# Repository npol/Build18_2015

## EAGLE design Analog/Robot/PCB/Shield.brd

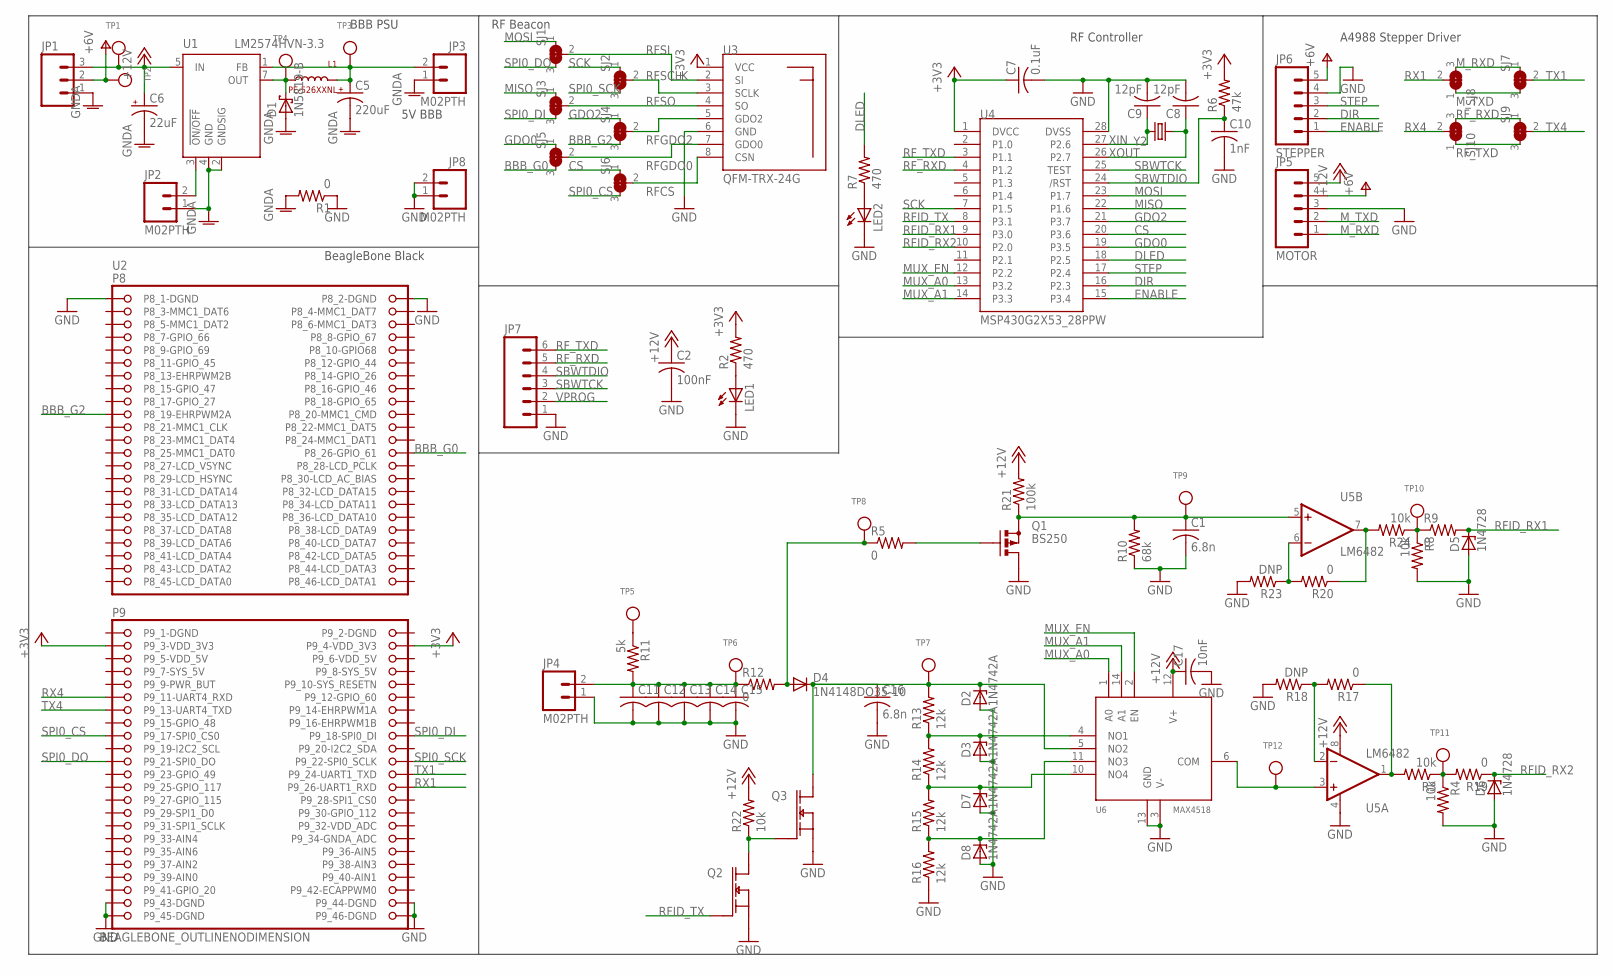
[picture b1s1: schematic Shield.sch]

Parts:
C1, C16: 6.8n; C0805
C2: 100nF; C0805
C5: 220uF; E3,5-8
C6: 22uF; E2,5-5
C7: 0.1uF; C0805
C8, C9: 12pF; C0805
C10: 1nF; C0805
C11, C12, C13, C14, C15: C-USC0805; C0805
C17: 10nF; C0805
D1: 1N5819-B; DO41-7.6
D2, D3, D7, D8: 1N4742A; DO41Z10
D4: 1N4148DO35-10; DO35-10
D5, D6: 1N4728; DO41Z10
JP1: M03PTH; 1X03
JP2, JP3, JP4, JP8: M02PTH; 1X02
JP5: MOTOR; 1X05
JP6: STEPPER; 1X05
JP7: M06SIP; 1X06
L1: PE-526XXNL; PE_VERTICAL
LED1, LED2: LEDCHIP-LED0805; CHIP-LED0805
Q1: BS250; SOT54E
Q2, Q3: 2N7002_SINGLESOT23/TO-236AB; TO-236AB
R1, R5, R9, R12, R17, R19, R20: 0; R0805
R2, R7: 470; R0805
R3, R4, R8, R22, R24: 10k; R0805
R6: 47k; R0805
R10: 68k; R0805
R11: 5k; R0805
R13, R14, R15, R16: 12k; R0805
R18, R23: DNP; R0805
R21: 100k; R0805
SJ1, SJ2, SJ3, SJ4, SJ5, SJ6, SJ7, SJ8, SJ9, SJ10: SOLDERJUMPER_2WAY0805; SOLDERJUMPER_2WAY_OPEN_0805
TP1, TP2, TP3, TP4, TP5, TP6, TP7, TP8, TP9, TP10, TP11, TP12: TESTPOINT0.1"; 1X01_ROUND
U1: LM2574HVN-3.3; DIL08
U2: BEAGLEBONE_OUTLINENODIMENSION; BEAGLEBONE_SHIELD_NODIMENSION
U3: QFM-TRX-24G; QFM-TRX1-24G
U4: MSP430G2X53_28PPW; PW(R-PDSO-G28)
U5: LM6482; SOIC8
U6: MAX4518; SO-14
Y2: CRYSTALHC49UV; HC49U-V

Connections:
+3V3: C7.1, R2.2, R6.2, U2.9.3 (P9_3-VDD_3V3), U2.9.4 (P9_4-VDD_3V3), U3.1 (VCC), U4.1 (DVCC)
+12V: C2.1, C6.+, C17.1, JP1.3, JP5.5, R21.2, R22.2, TP1.1, U1.5 (IN), U5.8 (V+), U6.12 (V+)
BBB_G0: SJ5.3, U2.8.26 (P8_26-GPIO_61)
BBB_G2: SJ4.3, U2.8.19 (P8_19-EHRPWM2A)
CS: SJ6.1, U4.20 (P3.6)
DIR: JP6.2, U4.16 (P2.3)
DLED: R7.2, U4.18 (P2.5)
ENABLE: JP6.1, U4.15 (P3.4)
GDO0: SJ5.1, U4.19 (P3.5)
GDO2: SJ4.1, U4.21 (P3.7)
GND: C1.2, C2.2, C7.2, C8.2, C9.2, C10.2, C11.2, C12.2, C13.2, C14.2, C15.2, C16.2, C17.2, D2.A, D3.A, D5.A, D6.A, D7.A, D8.A, JP4.1, JP5.3, JP6.4, JP7.1, JP8.1, JP8.2, LED1.C, LED2.C, Q1.D, Q2.2 (S), Q3.2 (S), R1.1, R4.2, R8.2, R10.1, R16.1, R18.2, R23.2, U2.8.1 (P8_1-DGND), U2.8.2 (P8_2-DGND), U2.9.43 (P9_43-DGND), U2.9.44 (P9_44-DGND), U2.9.45 (P9_45-DGND), U2.9.46 (P9_46-DGND), U3.6 (GND), U4.28 (DVSS), U5.4 (V-), U6.3 (V-), U6.13 (GND)
GNDA: C5.-, C6.-, D1.A, JP1.1, JP2.1, JP3.1, R1.2, U1.2 (GNDSIG), U1.4 (GND)
MISO: SJ3.1, U4.22 (P1.6)
MOSI: SJ1.1, U4.23 (P1.7)
MUX_A0: U4.13 (P3.2), U6.1 (A0)
MUX_A1: U4.14 (P3.3), U6.14 (A1)
MUX_EN: U4.12 (P2.2), U6.2 (EN)
M_RXD: JP5.1, SJ7.1, SJ8.3
M_TXD: JP5.2, SJ7.3, SJ8.1
unnamed: R11.1, TP5.1
unnamed: LED2.A, R7.1
unnamed: D1.C, L1.2, TP4.1, U1.7 (OUT)
unnamed: C5.+, JP3.2, L1.1, TP3.1, U1.1 (FB)
unnamed: JP2.2, U1.3 (!ON/OFF)
unnamed: TP12.1, U5.3 (+IN), U6.6 (COM)
unnamed: C11.1, C12.1, C13.1, C14.1, C15.1, JP4.2, R11.2, R12.1, TP6.1
unnamed: D4.A, R5.1, R12.2, TP8.1
unnamed: C16.1, D2.C, D4.C, Q3.3 (D), R13.2, TP7.1, U6.5 (NO2)
unnamed: R20.2, R23.1, U5.6 (-IN)
unnamed: R20.1, R24.2, U5.7 (OUT)
unnamed: R17.2, R18.1, U5.2 (-IN)
unnamed: R8.1, R9.1, R24.1, TP10.1
unnamed: R3.2, R17.1, U5.1 (OUT)
unnamed: R3.1, R4.1, R19.2, TP11.1
unnamed: D3.C, R13.1, R14.2, U6.4 (NO1)
unnamed: D7.C, R14.1, R15.2, U6.10 (NO4)
unnamed: D8.C, R15.1, R16.2, U6.11 (NO3)
unnamed: C1.1, Q1.S, R10.2, R21.1, TP9.1, U5.5 (+IN)
unnamed: Q2.3 (D), Q3.1 (G), R22.1
unnamed: Q1.G, R5.2
unnamed: LED1.A, R2.1
P9_1-DGND: U2.9.1 (P9_1-DGND)
P9_2-DGND: U2.9.2 (P9_2-DGND)
P9_5-VDD_5V: U2.9.5 (P9_5-VDD_5V)
P9_6-VDD_5V: U2.9.6 (P9_6-VDD_5V)
P9_7-SYS_5V: U2.9.7 (P9_7-SYS_5V)
P9_39-AIN0: U2.9.39 (P9_39-AIN0)
RFCS: SJ6.2, U3.8 (CSN)
RFGDO0: SJ5.2, U3.7 (GDO0)
RFGDO2: SJ4.2, U3.5 (GDO2)
RFID_RX1: D5.C, R9.2, U4.9 (P3.0)
RFID_RX2: D6.C, R19.1, U4.10 (P2.0)
RFID_TX: Q2.1 (G), U4.8 (P3.1)
RFSCLK: SJ2.2, U3.3 (SCLK)
RFSI: SJ1.2, U3.2 (SI)
RFSO: SJ3.2, U3.4 (SO)
RF_RXD: JP7.5, SJ9.1, SJ10.3, U4.4 (P1.2)
RF_TXD: JP7.6, SJ9.3, SJ10.1, U4.3 (P1.1)
RX1: SJ8.2, U2.9.26 (P9_26-UART1_RXD)
RX4: SJ10.2, U2.9.11 (P9_11-UART4_RXD)
SBWTCK: JP7.3, U4.25 (TEST)
SBWTDIO: C10.1, JP7.4, R6.1, U4.24 (/RST)
SCK: SJ2.1, U4.7 (P1.5)
SPI0_CS: SJ6.3, U2.9.17 (P9_17-SPI0_CS0)
SPI0_DI: SJ3.3, U2.9.18 (P9_18-SPI0_DI)
SPI0_DO: SJ1.3, U2.9.21 (P9_21-SPI0_DO)
SPI0_SCK: SJ2.3, U2.9.22 (P9_22-SPI0_SCLK)
STEP: JP6.3, U4.17 (P2.4)
TX1: SJ7.2, U2.9.24 (P9_24-UART1_TXD)
TX4: SJ9.2, U2.9.13 (P9_13-UART4_TXD)
V+: JP1.2, JP5.4, JP6.5, TP2.1
VPROG: JP7.2
XIN: C9.1, U4.27 (P2.6), Y2.2
XOUT: C8.1, U4.26 (P2.7), Y2.1

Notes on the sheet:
RF Controller
5V BBB
RF Beacon
A4988 Stepper Driver
BBB PSU
BeagleBone Black

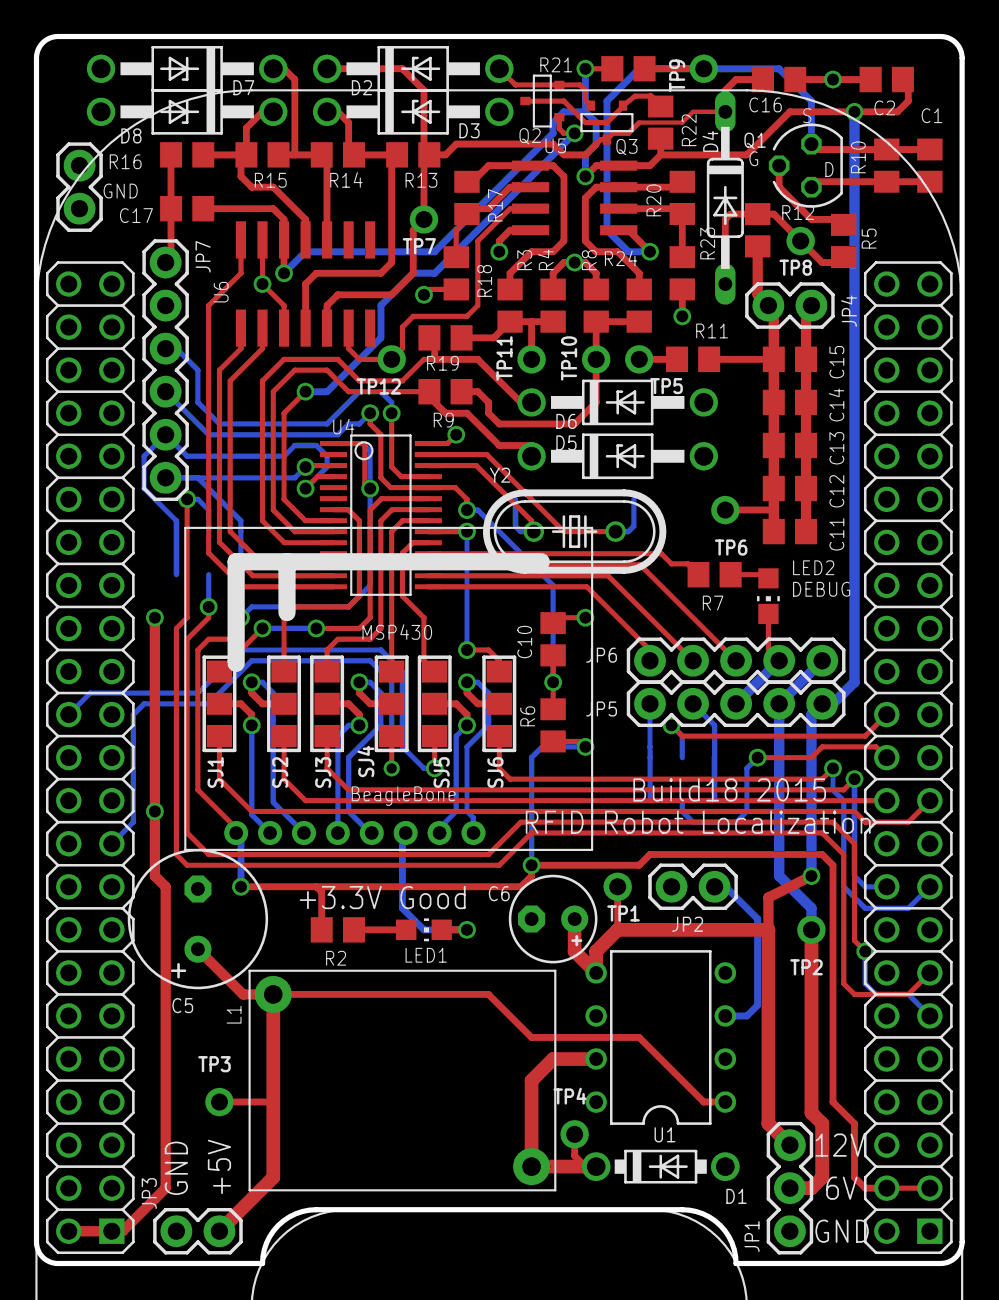
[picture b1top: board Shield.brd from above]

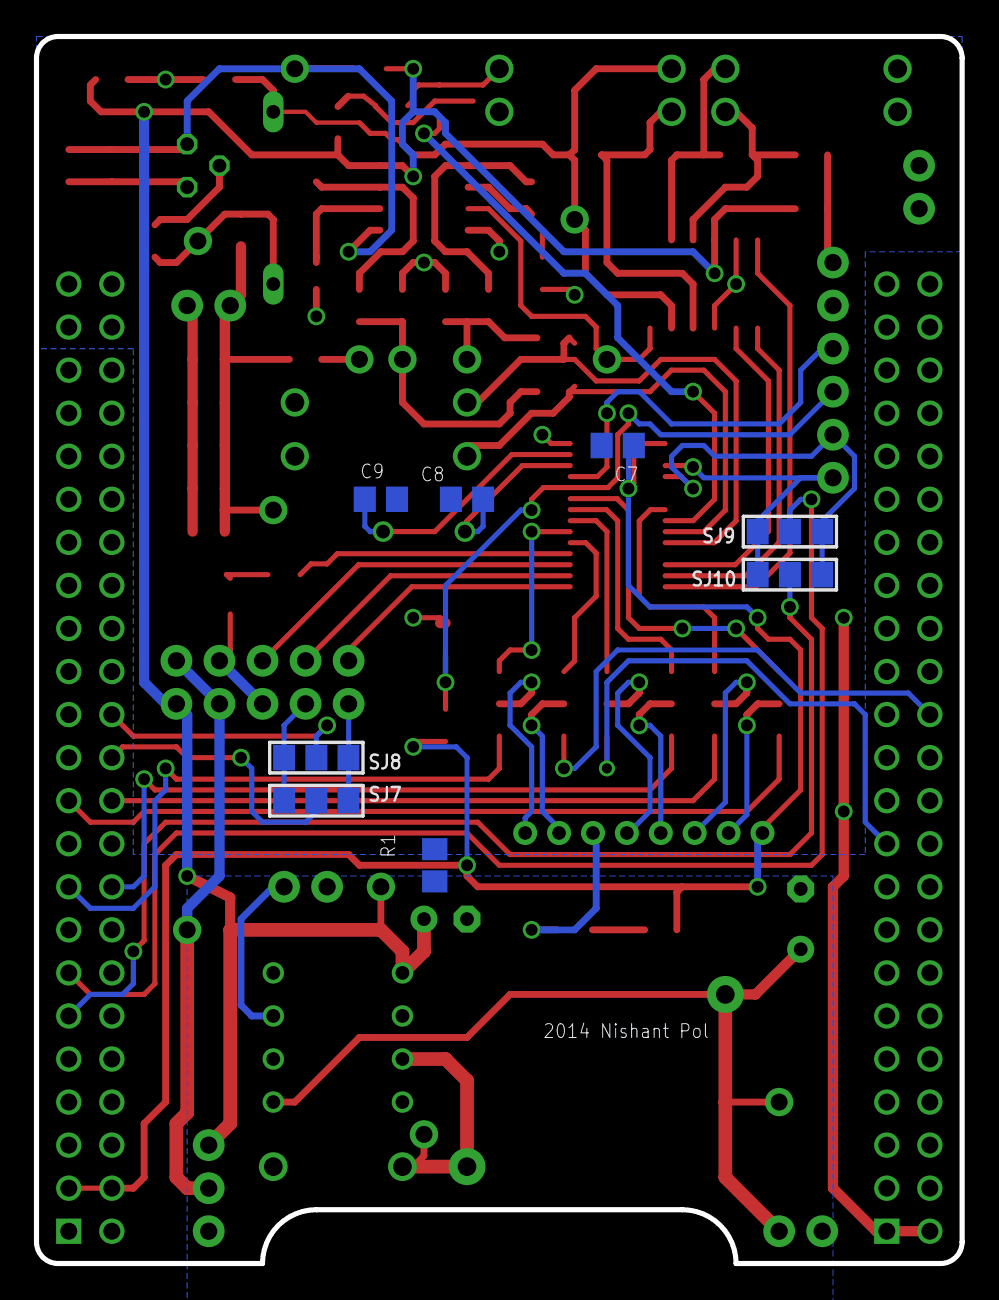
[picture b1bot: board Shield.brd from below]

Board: 2 copper layers, 54.6 x 72.4 mm, 90 parts (8 on the bottom side), 67 nets.

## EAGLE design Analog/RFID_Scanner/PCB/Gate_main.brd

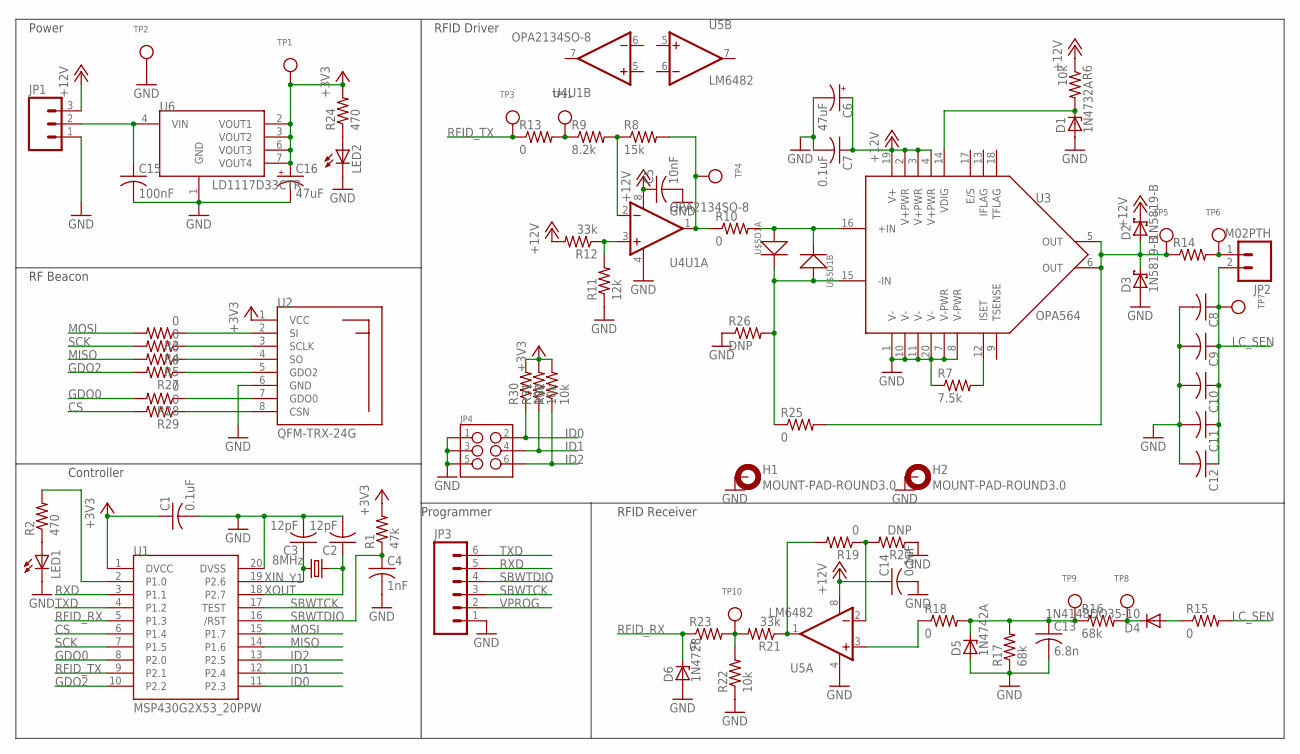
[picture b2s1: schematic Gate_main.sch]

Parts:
C1, C7, C14: 0.1uF; C0805
C2, C3: 12pF; C0805
C4: 1nF; C0805
C5: 10nF; C0805
C6, C16: 47uF; E2,5-6
C8, C9, C10, C11, C12: C-USC0805; C0805
C13: 6.8n; C0805
C15: 100nF; C0805
D1: 1N4732A; DO41Z10
D2, D3: 1N5819-B; DO41-7.6
D4: 1N4148DO35-10; DO35-10
D5: 1N4742A; DO41Z10
D6: 1N4728; DO41Z10
H1, H2: MOUNT-PAD-ROUND3.0; 3,0-PAD
JP1: M03PTH; 1X03
JP2: M02PTH; 1X02
JP3: M06SIP; 1X06
JP4: M03X22X3_SILK_SM; 2X3
LED1, LED2: LEDCHIPLED_0603; CHIPLED_0603
R1: 47k; R0805
R2, R24: 470; R0805
R3, R4, R5, R10, R13, R15, R18, R19, R23, R25, R27, R28, R29: 0; R0805
R6, R22, R30, R31, R32: 10k; R0805
R7: 7.5k; R0805
R8: 15k; R0805
R9: 8.2k; R0805
R11: 12k; R0805
R12, R21: 33k; R0805
R14: R-US_0207/10; 0207/10
R16, R17: 68k; R0805
R20, R26: DNP; R0805
TP1, TP2, TP3, TP4, TP5, TP6, TP7, TP8, TP9, TP10, TP11: TESTPOINT0.1"; 1X01_ROUND
U1: MSP430G2X53_20PPW; PW(R-PDSO-G20)
U2: QFM-TRX-24G; QFM-TRX1-24G
U3: OPA564; SO-20LD
U4: OPA2134SO-8; SOIC8
U5: LM6482; SOIC8
U6: LD1117D33CTR; SOIC8
U$5: SMS3922-015LF
Y1: 8MHz; HC49U-V

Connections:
+3V3: C1.1, C16.+, R1.2, R24.2, R30.2, R31.2, R32.2, TP1.1, U1.1 (DVCC), U2.1 (VCC), U6.2 (VOUT1), U6.3 (VOUT2), U6.6 (VOUT3), U6.7 (VOUT4)
+6V: C15.1, JP1.2, U6.4 (VIN)
+12V: C5.1, C6.+, C7.1, C14.1, D2.C, JP1.3, R6.1, R12.2, U3.2 (V+PWR), U3.3 (V+PWR), U3.4 (V+PWR), U3.19 (V+), U4.8 (V+), U5.8 (V+)
BIAS_OUT: R8.2, R10.1, TP4.1, U4.1 (OUT)
CS: R29.2, U1.6 (P1.4)
GDO0: R28.2, U1.8 (P2.0)
GDO2: R27.2, U1.10 (P2.2)
GND: C1.2, C2.2, C3.2, C4.2, C5.2, C6.-, C7.2, C8.2, C9.2, C10.2, C11.2, C12.2, C13.2, C14.2, C15.2, C16.-, D1.A, D3.A, D5.A, D6.A, H1.B3,0, H2.B3,0, JP1.1, JP3.1, JP4.1, JP4.3, JP4.5, LED1.C, LED2.C, R7.1, R11.1, R17.1, R20.1, R22.1, R26.1, TP2.1, U1.20 (DVSS), U2.6 (GND), U3.1 (V-), U3.7 (V-PWR), U3.8 (V-PWR), U3.10 (V-), U3.11 (V-), U3.20 (V-), U4.4 (V-), U5.4 (V-), U6.1 (GND)
ID0: JP4.2, R30.1, U1.11 (P2.3)
ID1: JP4.4, R31.1, U1.12 (P2.4)
ID2: JP4.6, R32.1, U1.13 (P2.5)
ISET: R7.2, U3.12 (ISET)
LC_SEN: C8.1, C9.1, C10.1, C11.1, C12.1, JP2.2, R15.2, TP7.1
MISO: R5.2, U1.14 (P1.6)
MOSI: R3.2, U1.15 (P1.7)
unnamed: LED1.A, R2.1
unnamed: R5.1, U2.4 (SO)
unnamed: R4.1, U2.3 (SCLK)
unnamed: R3.1, U2.2 (SI)
unnamed: R8.1, R9.2, U4.2 (-IN)
unnamed: R10.2, U3.16 (+IN), U$5.2 (K), U$5.4 (A)
unnamed: R11.2, R12.1, U4.3 (+IN)
unnamed: R9.1, R13.2, TP11.1
unnamed: JP2.1, R14.2, TP6.1
unnamed: D4.C, R16.2, TP8.1
unnamed: D4.A, R15.1
unnamed: R25.1, R26.2, U3.15 (-IN), U$5.1 (K), U$5.3 (A)
unnamed: C13.1, D5.C, R16.1, R17.2, R18.2, TP9.1
unnamed: R19.1, R20.2, U5.2 (-IN)
unnamed: R19.2, R21.1, U5.1 (OUT)
unnamed: R18.1, U5.3 (+IN)
unnamed: R21.2, R22.2, R23.2, TP10.1
unnamed: R2.2, U1.2 (P1.0)
unnamed: LED2.A, R24.1
unnamed: R29.1, U2.8 (CSN)
unnamed: R28.1, U2.7 (GDO0)
unnamed: R27.1, U2.5 (GDO2)
PA_OUT: D2.A, D3.C, R14.1, R25.2, TP5.1, U3.5 (OUT), U3.6 (OUT)
RFID_RX: D6.C, R23.1, U1.5 (P1.3)
RFID_TX: R13.1, TP3.1, U1.9 (P2.1)
RXD: JP3.5, U1.3 (P1.1)
SBWTCK: JP3.3, U1.17 (TEST)
SBWTDIO: C4.1, JP3.4, R1.1, U1.16 (/RST)
SCK: R4.2, U1.7 (P1.5)
TXD: JP3.6, U1.4 (P1.2)
VDIG: D1.C, R6.2, U3.14 (VDIG)
VPROG: JP3.2
XIN: C3.1, U1.19 (P2.6), Y1.2
XOUT: C2.1, U1.18 (P2.7), Y1.1

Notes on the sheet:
RFID Driver
RFID Receiver
Controller
RF Beacon
Power
Programmer

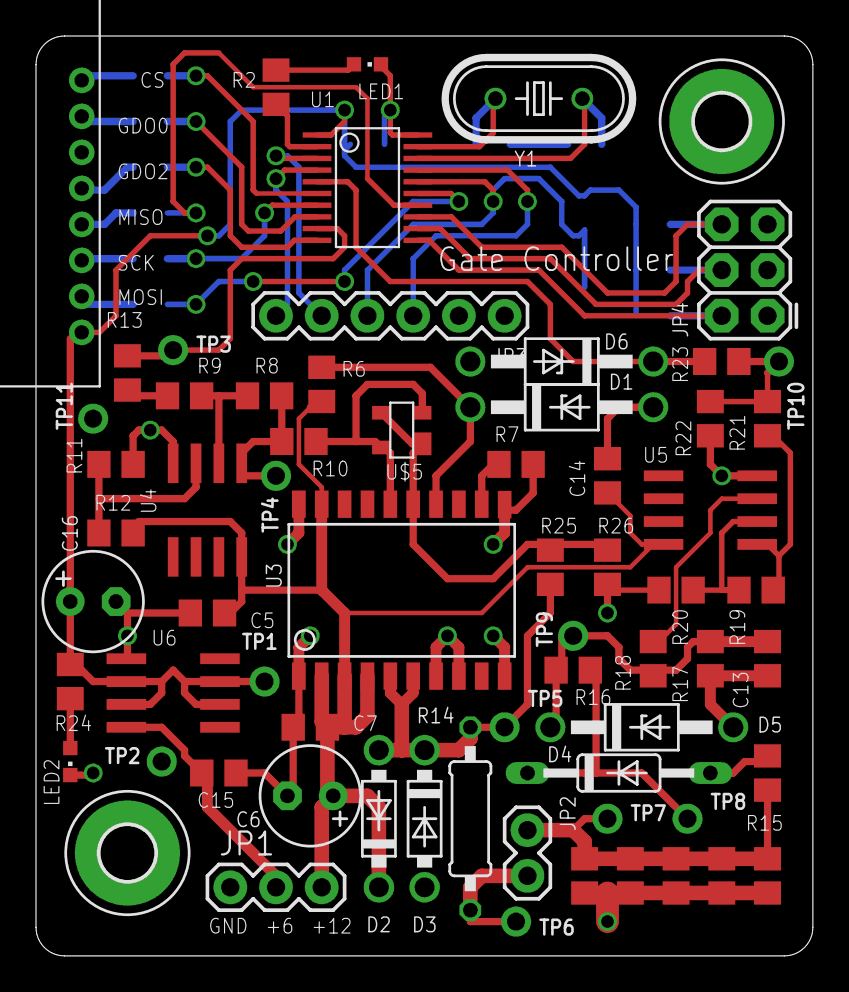
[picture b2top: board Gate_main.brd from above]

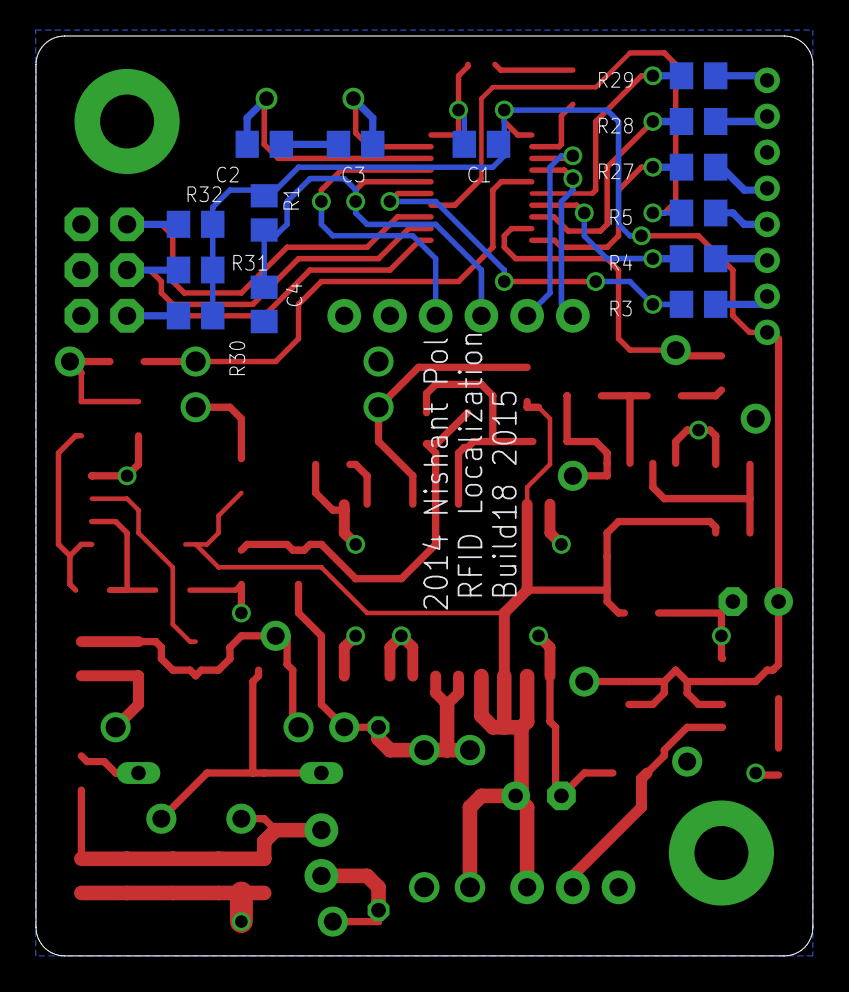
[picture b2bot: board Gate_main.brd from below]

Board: 2 copper layers, 43.2 x 51.1 mm, 81 parts (14 on the bottom side), 48 nets.

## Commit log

2014-11-20 :octocat: Added .gitattributes & .gitignore files
2014-11-20 RFID scanner output simulation
    Used CMOS inverter for bias, Sallen Key for LPF. Good LPF but biasing
    issues.
2014-11-21 RFID scanner output simulation
    Moved Inverter_SallenKey
    BiasAmp with Sallen Key works for ideal, triangle output for single
    supply
2014-11-21 RFID scanner output sim
    Fixed two issues with schematic: power ports were swapped, 741 has
    limited slew which caused it to give triangular output. Using LM318
    instead.
2014-11-21 RFID scanner output sim
    Fixed biasing stage and added 100ohm load. Output clips significantly,
    may want to use different PA
2014-11-25 RFID scanner in/out sim
    Output working, need to adjust resistor values to meet LM318 spec.
    Input is from 220 lab
2014-11-27 RFID scanner output sim and test
    Tested Output stage w/o load, using OPA132 as bias/filter amp, and
    OPA547 as power amp. 9V swing
2014-12-13 PCB and firmware
    Gate PCB 70% completed, need to figure out pinout for MCU and layout
    signal amps. Board size reduced by 50%. Also need to add testpoints
    Robot PCB PSU layout completed, motor and stepper drivers will move to
    separate PCB
    Created firmware files, w/o code
2014-12-13 Gate PCB progress
    Did layout for gate pcb signal amps, finalized board size, added
    testpoints
2014-12-30 Board final; SPI progress
    Sent PCBs to FAB
    SPI driver working for multi-byte. Bug: bytes are sent in reversed
    order, although bit ordering (MSB first) is correct.
2014-12-31 SPI progress
    SPI HAL layer tested: multi-byte tx and rx
    Linking: moved SPI and typedefs to separate files, tested
2014-12-31 SPI progress
    Started API for CC2500, tested strobe and partly read/write to config
    regs

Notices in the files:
parts and their libraries:
SparkFun-FreqCtrl: Licensing: CC v3.0 Share-Alike You are welcome to use this library for commercial purposes.
microbuilder: This work is placed in the public domain, and may be freely used for commercial and non-commercial work with the following conditions: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
